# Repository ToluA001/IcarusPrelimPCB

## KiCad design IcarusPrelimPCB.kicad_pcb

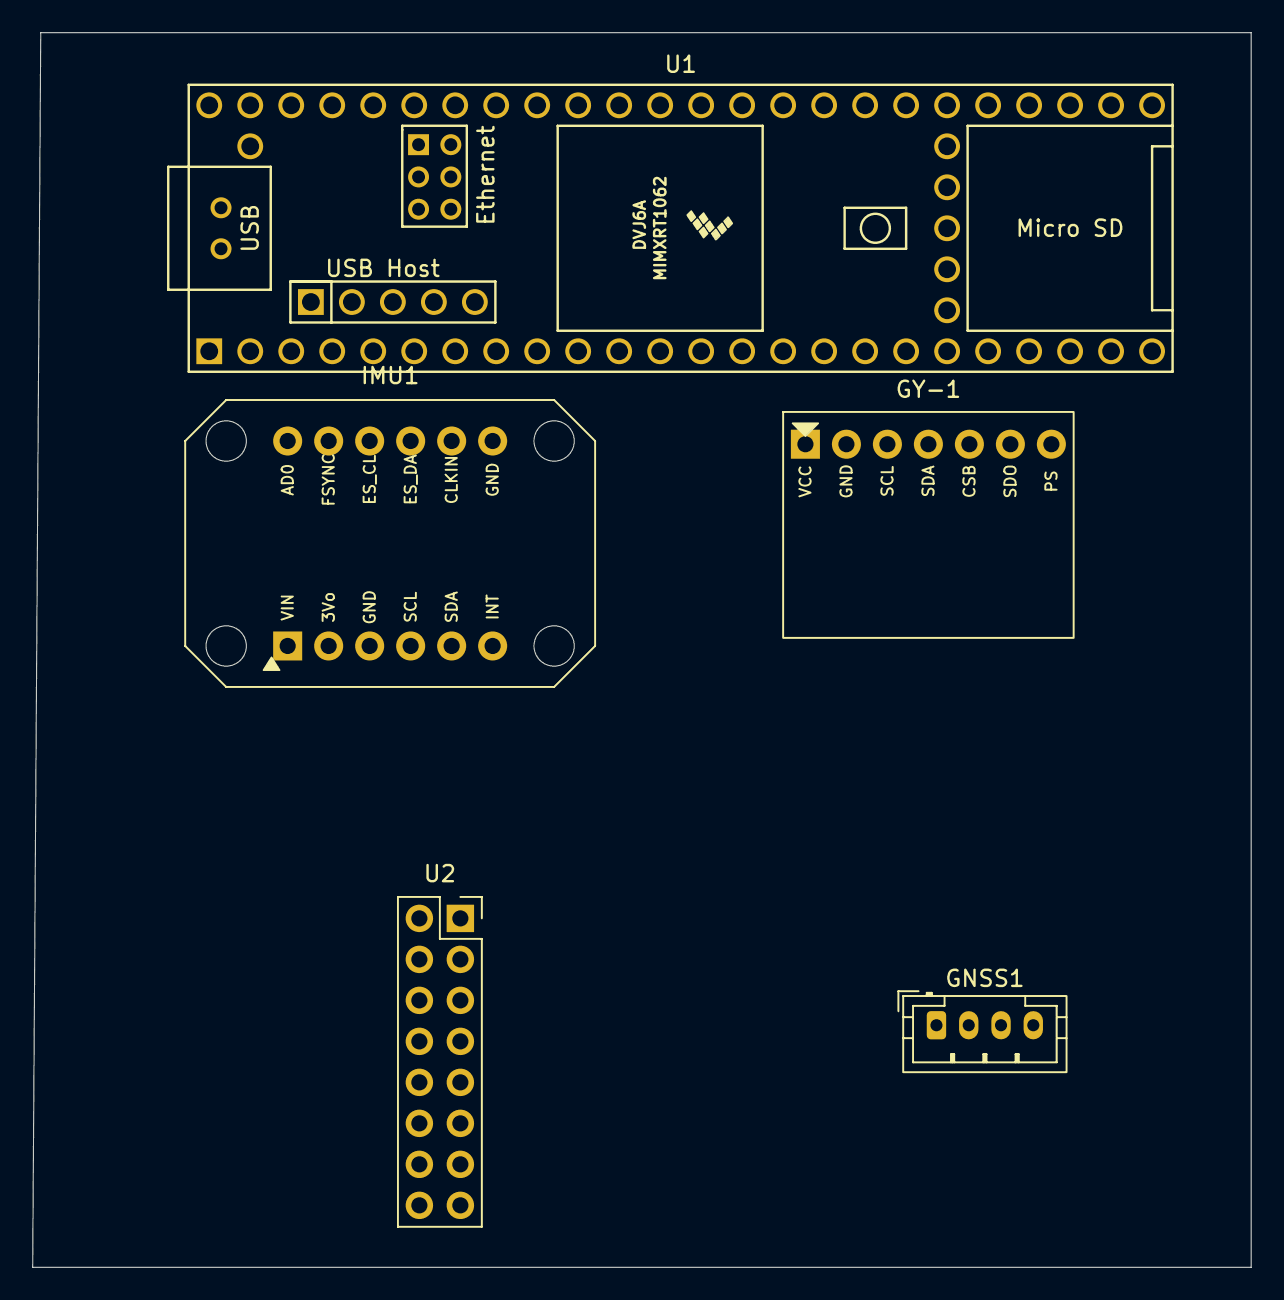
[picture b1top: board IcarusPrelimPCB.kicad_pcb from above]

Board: 2 copper layers, 75.5 x 76.5 mm, 5 parts (0 on the bottom side), 6 nets, no tracks yet.

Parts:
GNSS1: JST_PH_B4B-PH-K_1x04_P2.00mm_Vertical
GY-1: GY-63_MS5611_Breakout
IMU1: Adafruit_MPU6050_Breakout_3886
U1: Teensy4.1; Teensy41
U2: PinSocket_2x08_P2.54mm_Vertical

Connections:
GND: GNSS1.4 (GND), GY-1.7 (GND), IMU1.3 (GND), U1.47 (GND), U2.1 (GND), U2.2 (GND), U2.16 (GND)
unnamed: GNSS1.3 (SCL-RX), GY-1.2 (SCL), IMU1.4 (SCL), U1.41 (19_A5_SCL)
unnamed: GNSS1.2 (SDA-TX), GY-1.3 (SDA), IMU1.5 (SDA), U1.40 (18_A4_SDA)
unnamed: GNSS1.1 (VCC), GY-1.1 (VCC), IMU1.1 (VIN), U1.46 (3V3), U2.4 (VCC)
unnamed: U1.20 (28_RX7), U2.9 (Tx)
unnamed: U1.21 (29_TX7), U2.7 (Rx)
